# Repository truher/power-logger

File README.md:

# Power Logger

Multichannel logger for residential power consumption measurement.
Reads two legs of 120v and a whole log of inductive current measurements.
Uses interrupts on the Teensy to avoid phase error.

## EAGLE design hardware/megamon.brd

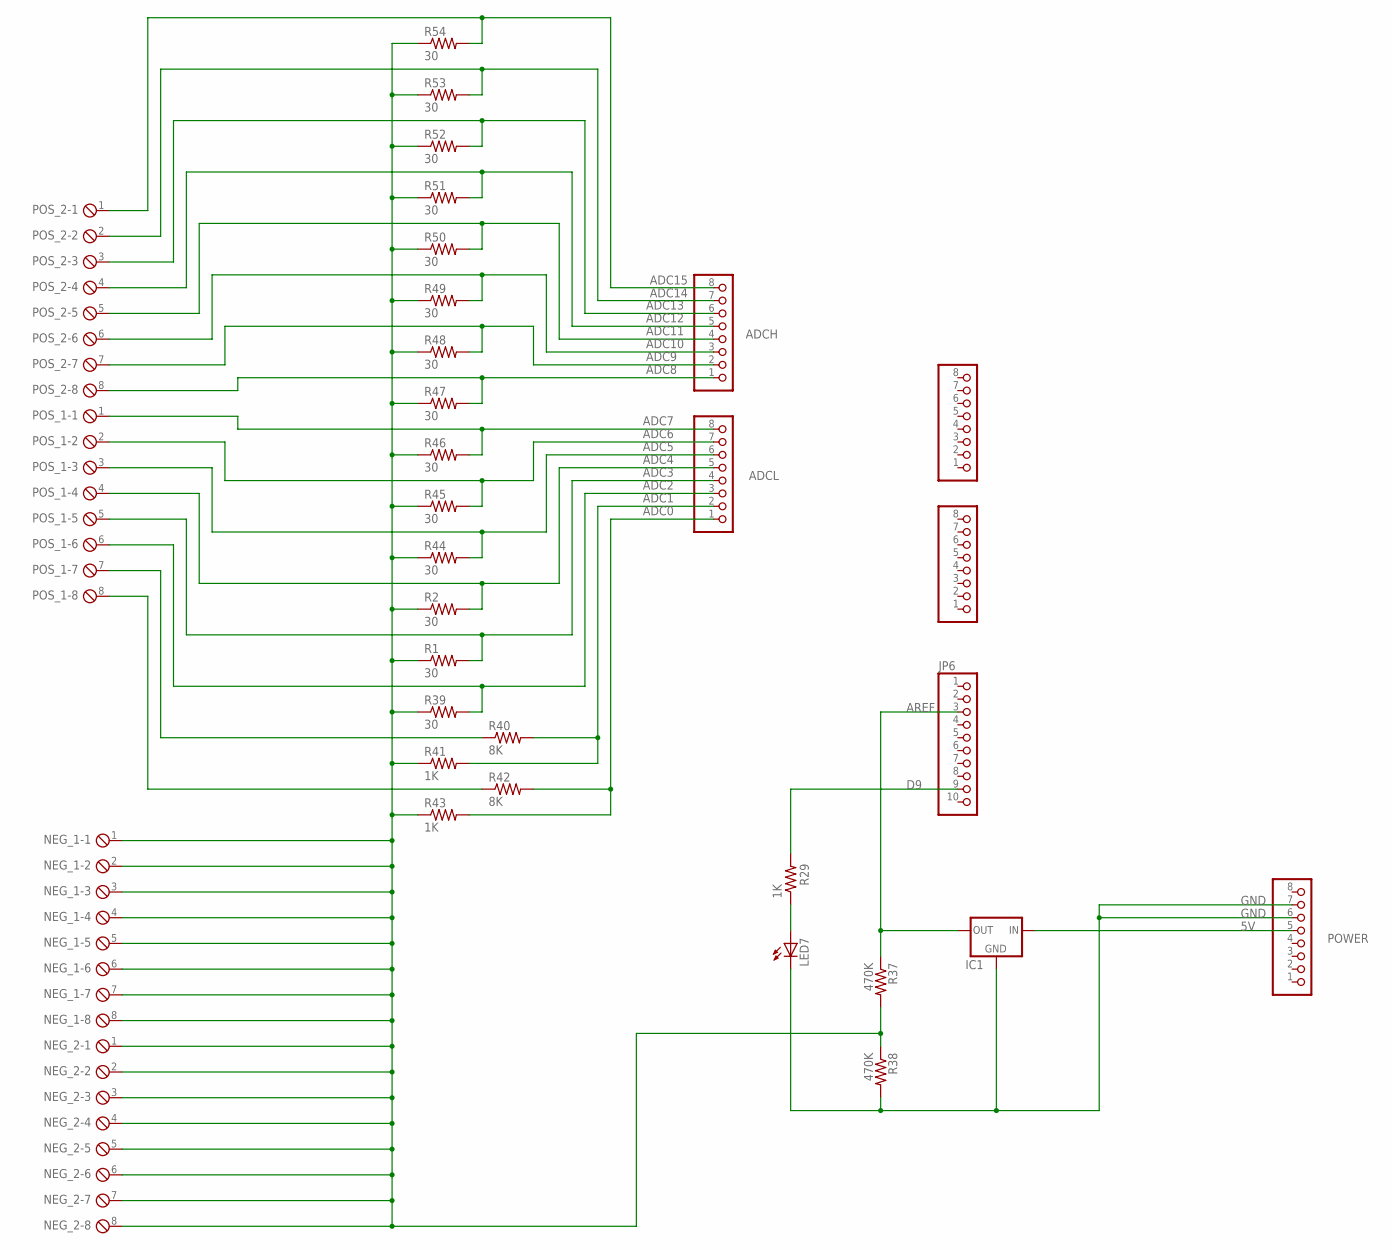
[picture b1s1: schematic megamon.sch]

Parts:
ADCH: PINHD-1X8; 1X08
ADCL: PINHD-1X8; 1X08
COMMUNICATION: FH254-108DF08500V; 1X08
IC1: MCP1700INLINE; TO92-INLINE
JP6: FH254-110DF08500V; 1X10
LED7: green; LED3MM
NEG_1, NEG_2: MPT8; 8POL254
POS_1, POS_2: MPT8; 8POL254
POWER: PINHD-1X8; 1X08
PWML: FH254-108DF08500V; 1X08
R1, R2, R39, R44, R45, R46, R47, R48, R49, R50, R51, R52, R53, R54: 30; 0204/7
R29, R41, R43: 1K; 0204/7
R37, R38: 470K; 0204/7
R40, R42: 8K; 0204/7

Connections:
5V: IC1.2 (IN), POWER.5
ADC0: ADCL.1, R42.2, R43.2
ADC1: ADCL.2, R40.2, R41.2
ADC2: ADCL.3, POS_1.6, R39.2
ADC3: ADCL.4, POS_1.5, R1.2
ADC4: ADCL.5, POS_1.4, R2.2
ADC5: ADCL.6, POS_1.3, R44.2
ADC6: ADCL.7, POS_1.2, R45.2
ADC7: ADCL.8, POS_1.1, R46.2
ADC8: ADCH.1, POS_2.8, R47.2
ADC9: ADCH.2, POS_2.7, R48.2
ADC10: ADCH.3, POS_2.6, R49.2
ADC11: ADCH.4, POS_2.5, R50.2
ADC12: ADCH.5, POS_2.4, R51.2
ADC13: ADCH.6, POS_2.3, R52.2
ADC14: ADCH.7, POS_2.2, R53.2
ADC15: ADCH.8, POS_2.1, R54.2
AREF: IC1.3 (OUT), JP6.3, R37.1
D9: JP6.9, R29.2
GND: IC1.1 (GND), LED7.K (C), POWER.6, POWER.7, R38.2
unnamed: POS_1.7, R40.1
unnamed: POS_1.8, R42.1
unnamed: LED7.A, R29.1
V_MID: NEG_1.1, NEG_1.2, NEG_1.3, NEG_1.4, NEG_1.5, NEG_1.6, NEG_1.7, NEG_1.8, NEG_2.1, NEG_2.2, NEG_2.3, NEG_2.4, NEG_2.5, NEG_2.6, NEG_2.7, NEG_2.8, R1.1, R2.1, R37.2, R38.1, R39.1, R41.1, R43.1, R44.1, R45.1, R46.1, R47.1, R48.1, R49.1, R50.1, R51.1, R52.1, R53.1, R54.1

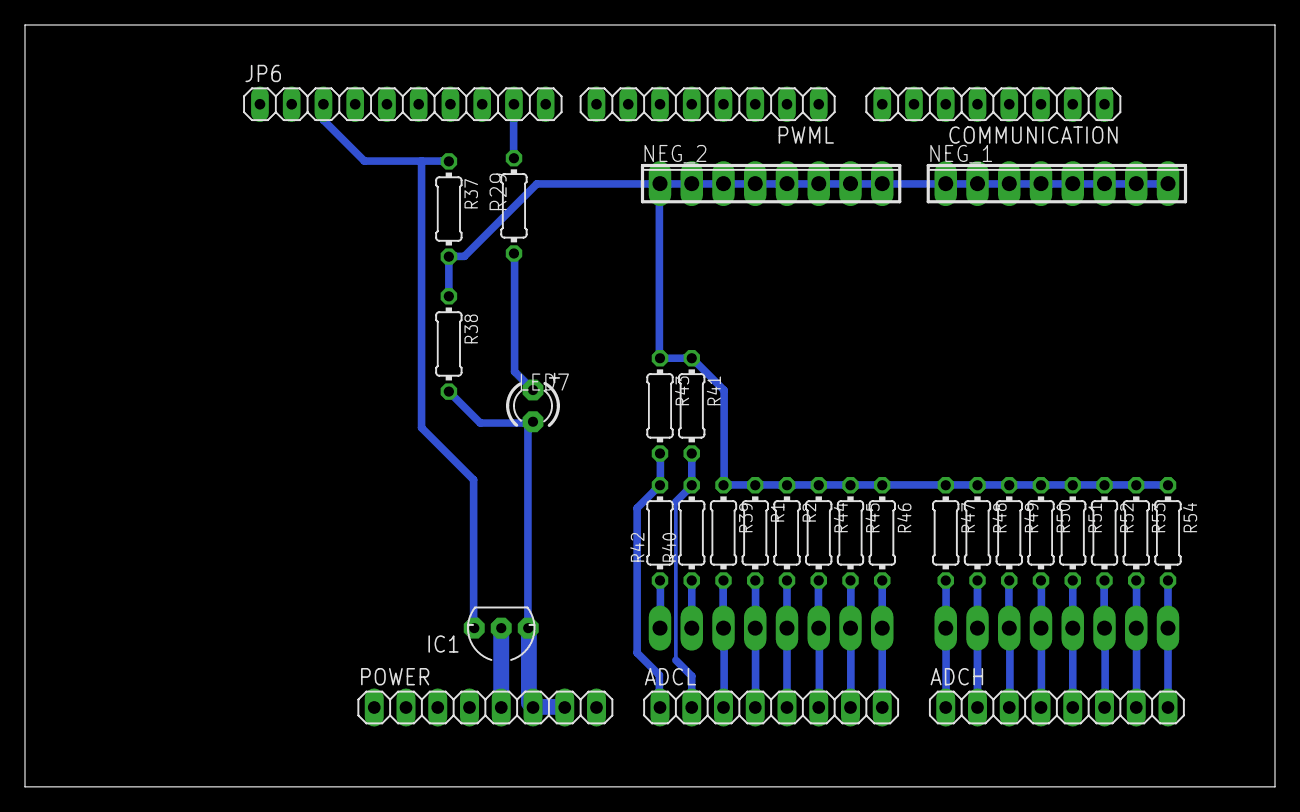
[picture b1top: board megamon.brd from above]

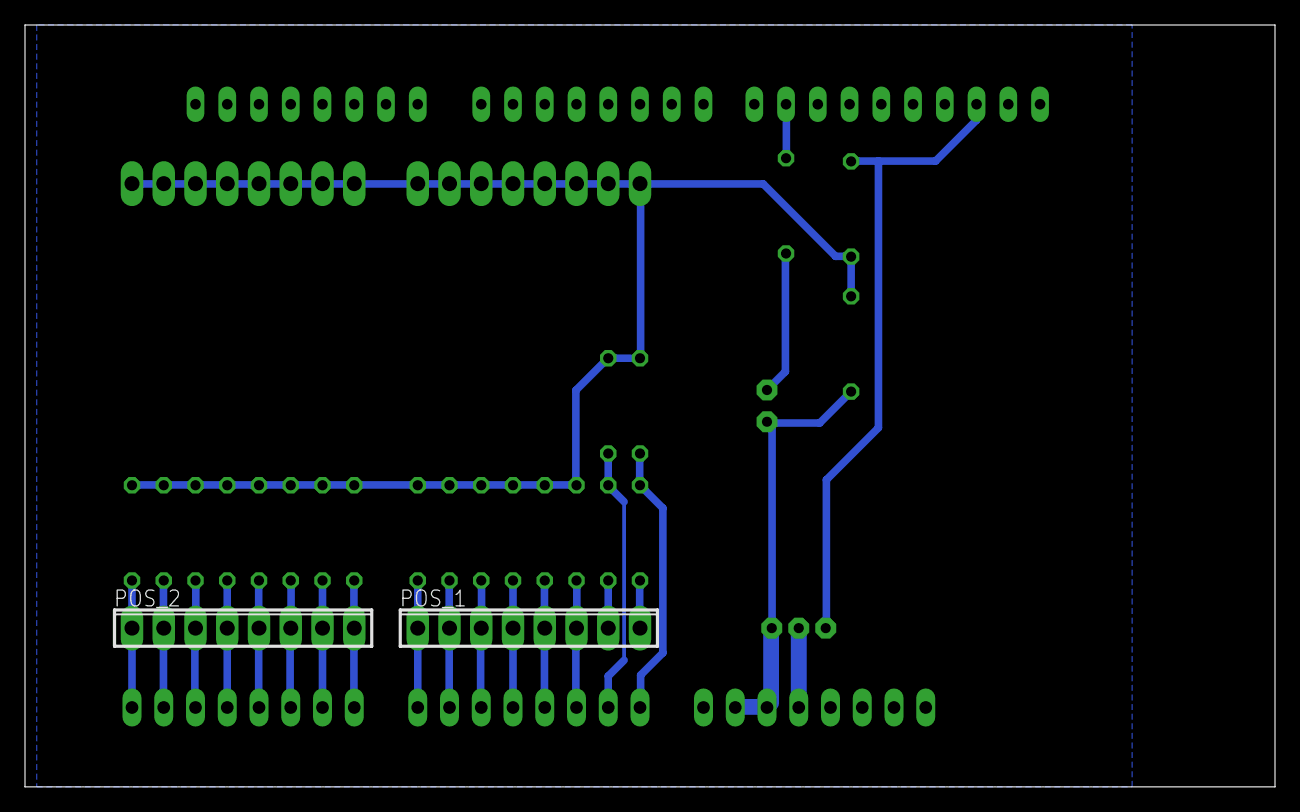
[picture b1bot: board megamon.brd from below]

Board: 2 copper layers, 100.0 x 61.0 mm, 33 parts (2 on the bottom side), 24 nets.

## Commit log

2020-04-05 matplotlib demo
2020-04-10 fiddling with plots
2020-04-10 more plot fixes
2020-04-10 add usb logger
2020-04-11 fix logger
2020-04-11 fix gitignore
2020-04-12 logger now hot pluggable
2020-04-12 fixed-width time
2020-04-13 now also read the datafile, using inotify
2020-04-13 clean up parsing and validation
2020-04-16 fiddling with plotting
2020-04-16 more plot fiddling
2020-04-16 minor fixes
2020-04-16 grouping
2020-04-16 commit experiments
2020-04-16 add example test
2020-04-16 multi-series experiment
2020-04-16 extract random generator
2020-04-16 comment test data
2020-04-17 example test
2020-04-17 move rollup to lib, test it
2020-04-17 removed, it was an exploration into the wrong way
2020-04-17 removed, superceded by later scripts
2020-04-17 remove plot example
2020-04-17 rename test data file
2020-04-17 remove plot experiment
2020-04-17 abandon mixed frequency resampling
2020-04-17 multiple threads, one frame? nah.
2020-04-17 remove file IO experiment
2020-04-17 formatting
2020-04-17 add multi-sensor random data
2020-04-18 add multi-sensor summarization, plot not done yet
2020-04-18 multi sensor plot works
2020-04-18 add monthly table
2020-04-18 don't pivot
2020-04-18 moving stuff to lib
2020-04-19 periodic summarizer works
2020-04-19 fix date format
2020-04-19 no more inotify
2020-04-19 rename
2020-04-19 move random data producers into standalone scripts
2020-04-19 remove single-sensor plotting
2020-04-21 mv to py dir
2020-04-22 very simple arduino now
2020-04-26 timer interrupt for sampling
    instead of running open-loop, use one of the avr timers in CTC
    mode, to interrupt exactly every 50us, so i don't have to keep
    the observation timestamps, and so can fit more observations
    in ram.
2020-04-26 hot-plug sensor usb faster
2020-04-26 handle v and i with timing offsets
2020-04-26 put the timeout back the way it was
    the short timeout results in partial lines i don't want to deal with
2020-04-26 fooling with delta encoding
2020-04-26 fix signed hex and fallthrough bugs
2020-04-26 decode delta and explode
2020-04-26 offset timing
2020-04-26 nice charts all done
2020-04-26 better handle error rows
2020-04-30 many small things
2020-04-30 performance testing
2020-05-03 got d3fc webgl rendering working
2020-05-03 performance testing python serialization
2020-05-03 checkpoint many small changes
2020-05-03 one more small change
2020-05-03 made webgl multis work with python data
    still not fast, but whatever, it can do ~10fps with some jank
2020-05-03 fix mypy
2020-05-04 works well enough at 10fps
    also handles partial data messages
2020-05-04 cleanups
2020-05-04 fix types
2020-05-04 cleaned up performance benchmarks
2020-05-04 woo, fixed d3fc error, now webgl goes 30fps
2020-05-05 little changes, no need for full fps
    it goes 4 fps with no real load anywhere
2020-05-05 remove obsolete demos
2020-05-06 working to finish the stuff in demo2
2020-05-06 more cleanups
2020-05-07 move stuff into lib
2020-05-07 hooked up sensors to VI charts, not fully
2020-05-07 multiple loads hooked up
2020-05-07 slower updates
2020-05-08 sensors now update archival data
    still messy and slow
2020-05-10 wrestling with d3 for awhile
2020-05-10 blag
2020-05-10 now works with server data
2020-05-10 cleanup
2020-05-10 moved summary charts to summary.html
2020-05-10 render three charts
2020-05-10 remove extra files
2020-05-10 working on rollups
2020-05-10 multiple graphs and summary table
    with correct windows.
2020-05-11 three pages working
    utc still broken
2020-05-11 combined css/js/html
2020-05-11 removed matplotlib
2020-05-11 fix test data
2020-05-11 add lib class to wrap serial readline
2020-05-12 add queue to transcriber
    still single thread
2020-05-12 separated reader and writer
2020-05-12 move interpolation etc out of transcribe
2020-05-12 removed transcriber
2020-05-12 oops, one more deletion
2020-05-12 threaded reads work
    consumer can be arbitrarily slow, but no corruption
2020-05-13 reduced cpu load by 10X, by sleeping between reads
    threaded reader was spinning faster than the sender
2020-05-14 simplify CSS
2020-05-15 got multis working better
2020-05-15 cleaned up js code
2020-05-15 remove demo code for sample interpolation
2020-05-15 remove another interp demo
2020-05-15 rm fastlogger
2020-05-15 clean up tests and test data
2020-05-15 move demos to demo repo
2020-05-15 rename test
2020-05-16 linted arduino, found i was overrunning sprintf
2020-05-16 stop using orjson, it doesn't work on ARM
2020-05-17 fixed everything pylint complained about
2020-05-17 remove obsolete test scripts
2020-05-18 speed up serialization
    larger buffer, fewer writes => less USB overhead
2020-05-18 was experimenting with shorter messages
    yes, overhead scales with message length.
2020-05-18 raw stats page, also cleanups
2020-05-18 fix js error
2020-05-22 make the emontx shield LED flash :-)
2020-05-22 looking harder at V and I
    multi graphs for "raw", zero = average, etc
2020-05-23 calibration done, graphs prettier, mypy happy
2020-05-23 fixed window in raw
    otherwise the trimmer makes it change all at once
2020-06-08 add mega shield schematic
2020-06-08 add schematic png
2020-06-09 replace ngspice components with real ones
2020-06-09 first cut at the board
2020-06-09 removed all but one LED
2020-06-09 replace pair terminals with separate pos/neg
2020-06-09 component placement done
2020-06-10 traces done, gnd plane done
2020-06-13 fix lib test
2020-06-13 beginning to move to mega
2020-06-14 remove the test stuff from config
2020-07-03 figured out FTM on teensy
2020-07-04 more progress
    FTM triggers an interrupt (to print) and both ADCs.
    when ADCs are done, they trigger an interrupt to extract the
    values.
    DMA is not started
2020-07-04 now DMA works
    so, timer -> ADC -> DMA, one buffer per USB input
2020-07-05 yay, it works now
    bunches of 1000 samples from 2 synchronized channels, yay!
2020-07-05 cleaned up, verified with scope, works great.
    two sync'ed channel ADC with DMA, sample timing uses timer,
    batch timing is not controlled.
2020-07-06 now outputs base85 from arduino
    tried decoding a few with python, works fine.
2020-07-06 oops, remove the old printing
2020-07-06 hooked up teensy to the python part
    threw out the interpolation stuff, works fine, just one ADC though.
2020-07-06 one led flash per sample, not toggled
2020-07-06 remove AVR arduino
2020-07-06 use teensy arduino
2020-07-06 starting to fix the lint
2020-07-06 more linting
2020-07-06 lint all done
2020-07-08 partial on-the-fly configuration of ADC parameters
2020-07-08 variable length now works
    but not yet in the web UI
2020-07-09 a bit more on config
2020-07-09 add variable freq
2020-07-10 prevent overflow
2020-07-12 calibrated ADC frequencies
    1khz to 150khz seems to work, single-ended.
2020-07-12 fixed sample timing
    the teensy code default is 4x averaging, so i turned that off
    now it goes about 500khz, 2us sample time, plenty of noise at
    that speed, but whatever.
2020-07-13 front end can adjust freq and length
    and updates at a reasonable rate as well
2020-07-14 adding channel details
2020-07-14 a bit more progress on channels
2020-07-15 finished channels
    they seem to work, need to test them.
2020-07-15 moved to ftm1 to make room for a8
2020-07-16 a little cleanup
2020-07-16 playing with kicad
2020-07-17 still learning kicad
2020-07-17 added more to sch
2020-07-17 more wiring
2020-07-18 fully routed
    ugly, but correct, i think.
2020-07-18 good looking board now
2020-07-19 sch and pcb look good, also gbr and ngc outputs
2020-07-19 fiddling with pcb2gcode
2020-07-21 hoo boy, adc protection and bigger terminals
2020-07-21 layout
2020-07-22 prettier traces, removed smt thing
2020-07-22 a little more beauty
2020-07-23 updated gbr and ngc
2020-07-25 DXF files
2020-07-25 add "map" file
2020-07-26 better gcodes
2020-07-29 whoops, lower zchange
2020-07-29 lower feed, smaller bit, more passes
2020-07-29 back to zero extra passes
2020-08-08 disable optimize
2020-08-08 retract 0.1, nog64
2020-08-08 faster feed, don't wait for spindle spin up or down
2020-08-08 add post-processor to remove M6
2020-08-08 less z
2020-08-08 remove M0
2020-08-08 remove a few more unnecessary gcode commands
2020-08-08 50 thou is way too deep
2020-08-09 bigger pads, bigger mill
2020-08-09 many more passes
2020-08-09 pcb is more than 10 thou thick
2020-08-09 remove offending M6 from drill
2020-08-09 got outline working
2020-08-09 add outline bridges
2020-08-10 2.54 rather than 3.5mm screws, now fits in 3x5
2020-08-23 removed some resistors i don't need
2020-08-23 moved a few traces
2020-08-23 gerbers
2020-09-06 settings for 0.1 cutters
    slower, finer
2020-09-06 minor tweaks
2020-09-06 wider cuts, fewer of them, deeper
2020-09-07 accommodate actual 27 mil bit
2020-09-07 tweaking after first copper run
2020-09-08 add workholding gcode
2020-09-10 add tooling cutout
2020-09-11 faster deeper
2020-09-12 tweaks
    mostly annoyed with ragged edges; try shallower, conventional cut
2020-10-05 formatting for printing
2020-10-12 fix js references
2020-10-12 use correct teensy ID number
2020-10-12 why does DAC1_C0 crash the teensy?
2020-10-12 correct decode method name
2020-10-13 arduino channels now match hardware
    i changed the routing to make it easier to lay out
2020-10-14 fixed channel config
    differential was on the wrong channel, also reported on wrong output
2020-10-17 ignore first few samples since they're bad
    at least the first one is. ignoring 4 makes b85 happy.
2020-10-17 add capacitor for bias smoothing
2020-10-24 add median
    haven't used it yet
2020-10-24 various filtering attempts
2020-10-24 use std kth_element instead of my own quickselect
2020-10-25 tweaking to reduce noise
2020-10-25 remove filtering/phase correction
2020-10-25 phase lag both V and A
2020-11-08 fix the kicad, also tuning
